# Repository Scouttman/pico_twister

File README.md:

# pico_twister
A simple BLDC motor driver based on the RP2040
Developed using kicad nightly and seem to crash current kicad release(as of 2022)
Currently non functional and just added current sense

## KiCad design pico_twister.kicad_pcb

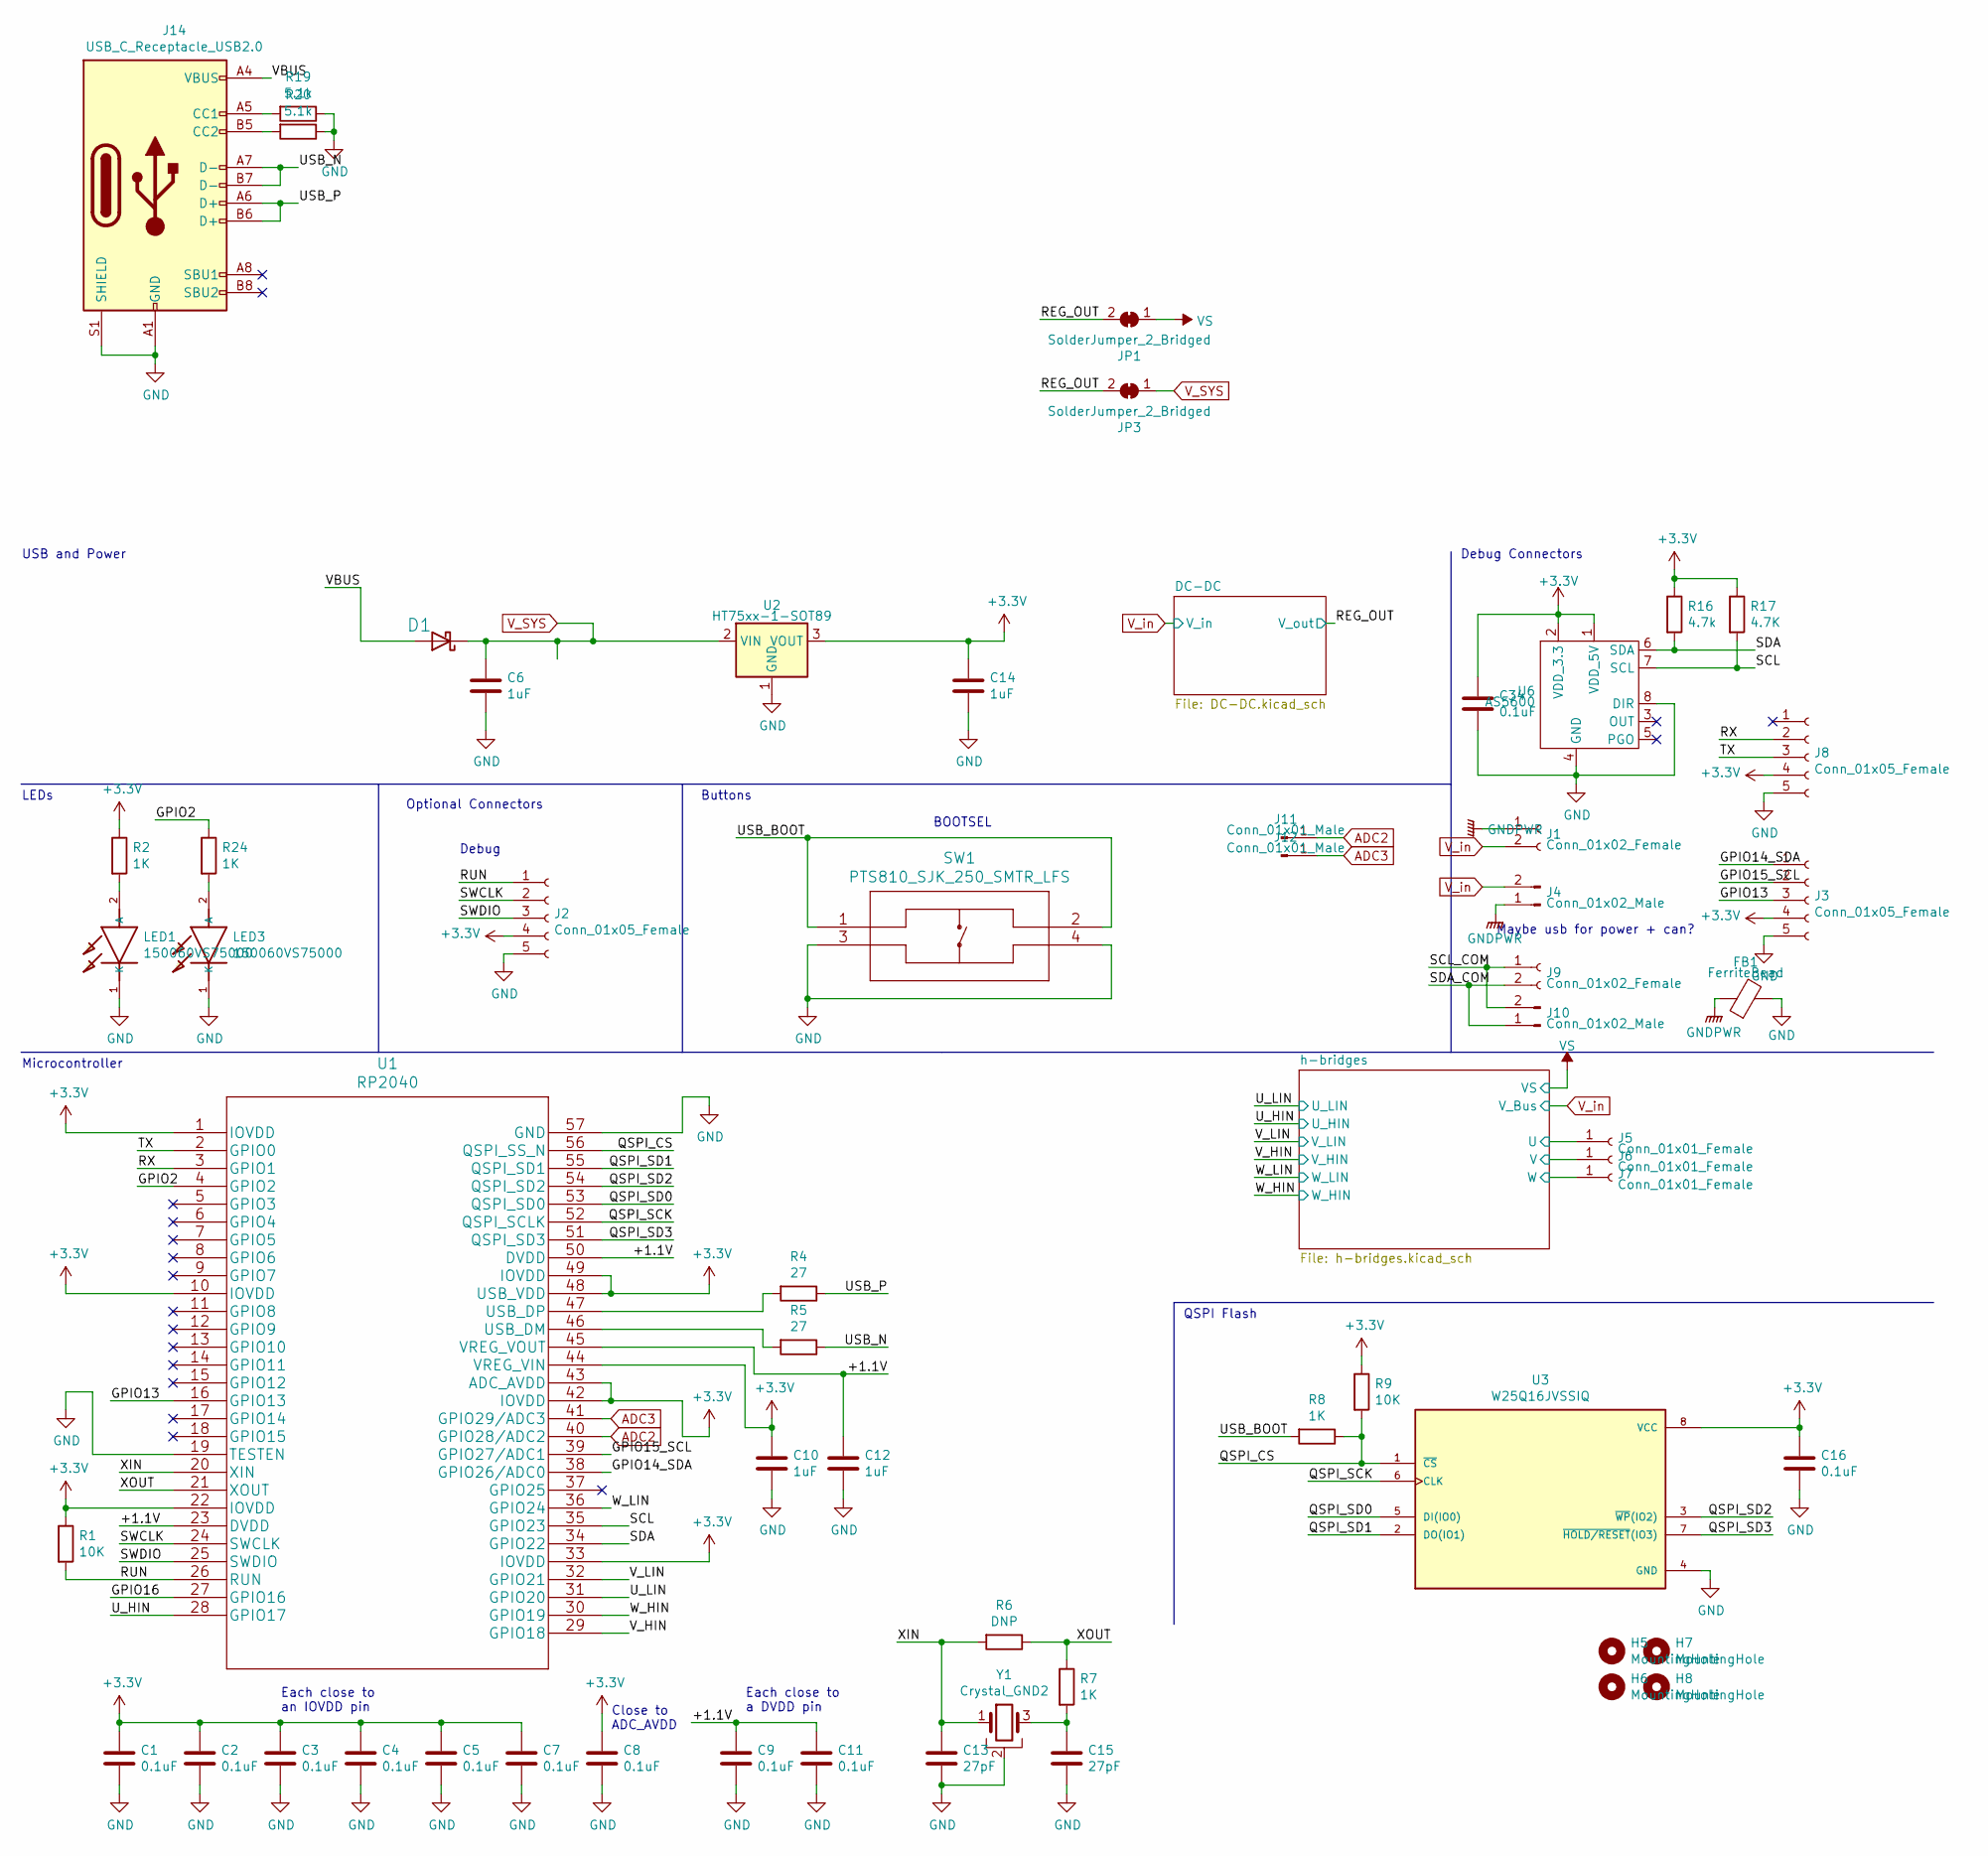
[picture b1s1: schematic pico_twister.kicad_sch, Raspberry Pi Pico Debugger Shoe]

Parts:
C1, C2, C3, C4, C5, C7, C8, C9, C11, C16, C34: 0.1uF; C_0603_1608Metric_Pad1.08x0.95mm_HandSolder; Digi-Key_PN 311-1344-1-ND
C6, C10, C12, C14: 1uF; C_0603_1608Metric_Pad1.08x0.95mm_HandSolder; Digi-Key_PN 1276-6524-1-ND
C13, C15: 27pF; C_0603_1608Metric_Pad1.08x0.95mm_HandSolder; Digi-Key_PN 311-1063-1-ND
D1: B5819W SL; D_SOD-123; LCSC C8598
FB1: FerriteBead; R_0603_1608Metric; LCSC Part C1002
H5, H6, H7, H8: MountingHole; MountingHole_3.2mm_M3
J1: Conn_01x02_Female; AMASS_XT30PW-F_1x02_P2.50mm_Horizontal
J2, J3, J8: Conn_01x05_Female; JST_SH_SM05B-SRSS-TB_1x05-1MP_P1.00mm_Horizontal; LCSC Part C145957
J4: Conn_01x02_Male; AMASS_XT30PW-M_1x02_P2.50mm_Horizontal
J5, J6, J7: Conn_01x01_Female; Pin_D1.4mm_L8.5mm_W2.8mm_FlatFork
J9: Conn_01x02_Female
J10: Conn_01x02_Male
J11, J12: Conn_01x01_Male; TestPoint_Pad_1.0x1.0mm
J14: USB_C_Receptacle_USB2.0; USB_C_Receptacle_XKB_U262-16XN-4BVC11; LCSC Part C167321
JP1, JP3: SolderJumper_2_Bridged; SolderJumper-2_P1.3mm_Bridged_RoundedPad1.0x1.5mm
LED1: 150060VS75000; LED_0805_2012Metric; MOUSER_PART_NUMBER 710-150060VS75000
LED3: 150060VS75000; LED_0805_2012Metric_Castellated; MOUSER_PART_NUMBER 710-150060VS75000
R1, R9: 10K; R_0603_1608Metric_Pad0.98x0.95mm_HandSolder; Digi-Key_PN 311-10KGRCT-ND
R2, R24: 1K; R_0603_1608Metric; Digi-Key_PN 311-1.00KHRCT-ND
R4, R5: 27; R_0603_1608Metric_Pad0.98x0.95mm_HandSolder; Digi-Key_PN 311-27.0HRCT-ND
R6: DNP; R_0603_1608Metric_Pad0.98x0.95mm_HandSolder
R7, R8: 1K; R_0603_1608Metric_Pad0.98x0.95mm_HandSolder; Digi-Key_PN 311-1.00KHRCT-ND
R16: 4.7k; R_0603_1608Metric_Pad0.98x0.95mm_HandSolder; LCSC Part C23162
R17: 4.7K; R_0603_1608Metric_Pad0.98x0.95mm_HandSolder; LCSC Part C23162
R19, R20: 5.1k; R_0603_1608Metric; LCSC Part C23186
SW1: PTS810_SJK_250_SMTR_LFS; SW_SPST_PTS810; Digi-Key_PN CKN10503CT-ND
U1: RP2040; Digi-Key_PN TBD
U2: HT75xx-1-SOT89; SOT-89-3; LCSC Part C14289
U3: W25Q16JVSSIQ; SOIC127P790X216-8N; Digi-Key_PN 256-W25Q16JVSSIM-ND
U6: AS5600; SOIC-8_3.9x4.9mm_P1.27mm
Y1: Crystal_GND2; Crystal_SMD_3225-4Pin_3.2x2.5mm; LCSC Part C9002

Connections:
/+1.1V: C9.1, C11.1, C12.1, U1.23 (DVDD), U1.45 (VREG_VOUT), U1.50 (DVDD)
/GPIO2: R24.1, U1.4 (GPIO2)
/GPIO13: J3.3, U1.16 (GPIO13)
/GPIO14_SDA: J3.1, U1.38 (GPIO26/ADC0)
/GPIO15_SCL: J3.2, U1.39 (GPIO27/ADC1)
/GPIO16: U1.27 (GPIO16)
/QSPI_CS: R8.1, R9.2, U1.56 (QSPI_SS_N), U3.1 (~CS)
/QSPI_SCK: U1.52 (QSPI_SCLK), U3.6 (CLK)
/QSPI_SD0: U1.53 (QSPI_SD0), U3.5 (DI(IO0))
/QSPI_SD1: U1.55 (QSPI_SD1), U3.2 (DO(IO1))
/QSPI_SD2: U1.54 (QSPI_SD2), U3.3 (~WP(IO2))
/QSPI_SD3: U1.51 (QSPI_SD3), U3.7 (~HOLD/RESET(IO3))
/REG_OUT: JP1.2 (B), JP3.2 (B); also elsewhere on the board
/RUN: J2.1, R1.2, U1.26 (RUN)
/RX: J8.2, U1.3 (GPIO1)
/SCL: R17.2, U1.35 (GPIO23), U6.7 (SCL)
/SDA: R16.2, U1.34 (GPIO22), U6.6 (SDA)
/SWCLK: J2.2, U1.24 (SWCLK)
/SWDIO: J2.3, U1.25 (SWDIO)
/TX: J8.3, U1.2 (GPIO0)
/USB_BOOT: R8.2, SW1.1, SW1.2
/USB_N: J14.A7 (D-), J14.B7 (D-), R5.1
/USB_P: J14.A6 (D+), J14.B6 (D+), R4.1
/U_HIN: U1.28 (GPIO17); also elsewhere on the board
/U_LIN: U1.31 (GPIO20); also elsewhere on the board
/VBUS: D1.2 (A), J14.A4 (VBUS), J14.A9 (VBUS), J14.B4 (VBUS), J14.B9 (VBUS)
/V_HIN: U1.29 (GPIO18); also elsewhere on the board
/V_LIN: U1.32 (GPIO21); also elsewhere on the board
/W_HIN: U1.30 (GPIO19); also elsewhere on the board
/W_LIN: U1.36 (GPIO24); also elsewhere on the board
/XIN: C13.1, R6.2, U1.20 (XIN), Y1.1
/XOUT: R6.1, R7.1, U1.21 (XOUT)
/h-bridges/VS_U: J5.1; also elsewhere on the board
/h-bridges/VS_V: J6.1; also elsewhere on the board
/h-bridges/VS_W: J7.1; also elsewhere on the board
ADC2: J11.1, U1.40 (GPIO28/ADC2); also elsewhere on the board
ADC3: J12.1, U1.41 (GPIO29/ADC3)
GND: C1.2, C2.2, C3.2, C4.2, C5.2, C6.2, C7.2, C8.2, C9.2, C10.2, C11.2, C12.2, C13.2, C14.2, C15.2, C16.2, C34.2, FB1.2, J2.5, J3.5, J8.5, J14.A1 (GND), J14.A12 (GND), J14.B1 (GND), J14.B12 (GND), J14.S1 (SHIELD), LED1.1 (K), LED3.1 (K), R19.1, R20.1, SW1.3, SW1.4, U1.19 (TESTEN), U1.57 (GND), U2.1 (GND), U3.4 (GND), U6.4 (GND), U6.8 (DIR), Y1.2; also elsewhere on the board
GNDPWR: FB1.1, J1.1, J4.1; also elsewhere on the board
unnamed: C15.1, R7.2, Y1.3
unnamed: J9.2, J10.1
unnamed: J9.1, J10.2
unnamed: J14.A5 (CC1), R19.2
unnamed: J14.B5 (CC2), R20.2
unnamed: LED1.2 (A), R2.2
unnamed: LED3.2 (A), R24.2
unnamed: R5.2, U1.46 (USB_DM)
unnamed: R4.2, U1.47 (USB_DP)
VS: JP1.1 (A); also elsewhere on the board
V_SYS: C6.1, D1.1 (K), JP3.1 (A), U2.2 (VIN)
V_in: J1.2, J4.2; also elsewhere on the board

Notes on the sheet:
Optional Connectors
USB and Power
Debug Connectors
QSPI Flash
Debug
Each close to a DVDD pin
Buttons
LEDs
Each close to an IOVDD pin
Maybe usb for power + can?
Close to ADC_AVDD
Microcontroller
BOOTSEL

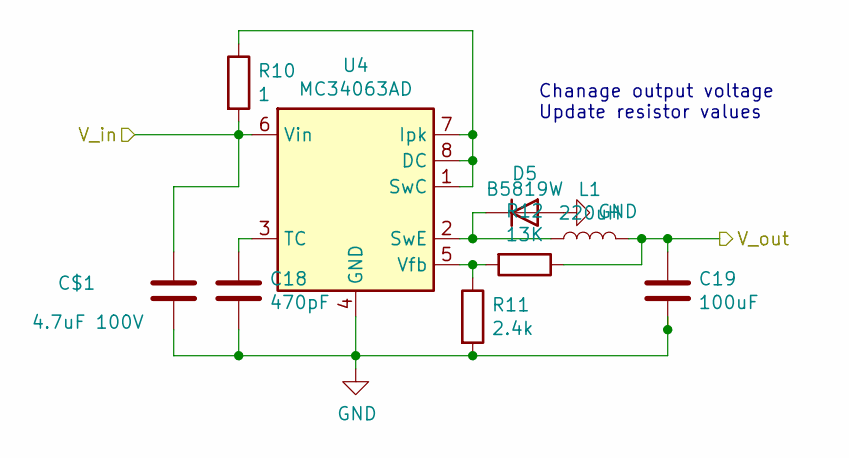
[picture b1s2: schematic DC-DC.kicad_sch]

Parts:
C18: 470pF; C_0603_1608Metric; LCSC Part C1620
C19: 100uF; C_1206_3216Metric; LCSC Part C312983
C$1: 4.7uF 100V; C_1210_3225Metric; LCSC C697607
D5: B5819W; D_SOD-123; LCSC Part C8598
L1: 220uH; SCCD43; LCSC Part C532867
R10: 1; R_0603_1608Metric; LCSC Part C22936
R11: 2.4k; R_0603_1608Metric; LCSC Part C22940
R12: 13K; R_0603_1608Metric; LCSC Part C22797
U4: MC34063AD; SOIC-8_3.9x4.9mm_P1.27mm; LCSC Part C32078

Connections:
/REG_OUT: C19.2, L1.2, R12.1; also elsewhere on the board
GND: C18.2, C19.1, C$1.2, D5.2 (A), R11.2, U4.4 (GND); also elsewhere on the board
unnamed: D5.1 (K), L1.1, U4.2 (SwE)
unnamed: R10.1, U4.1 (SwC), U4.7 (Ipk), U4.8 (DC)
unnamed: C18.1, U4.3 (TC)
unnamed: R11.1, R12.2, U4.5 (Vfb)
V_in: C$1.1, R10.2, U4.6 (Vin); also elsewhere on the board

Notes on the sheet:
Chanage output voltage Update resistor values

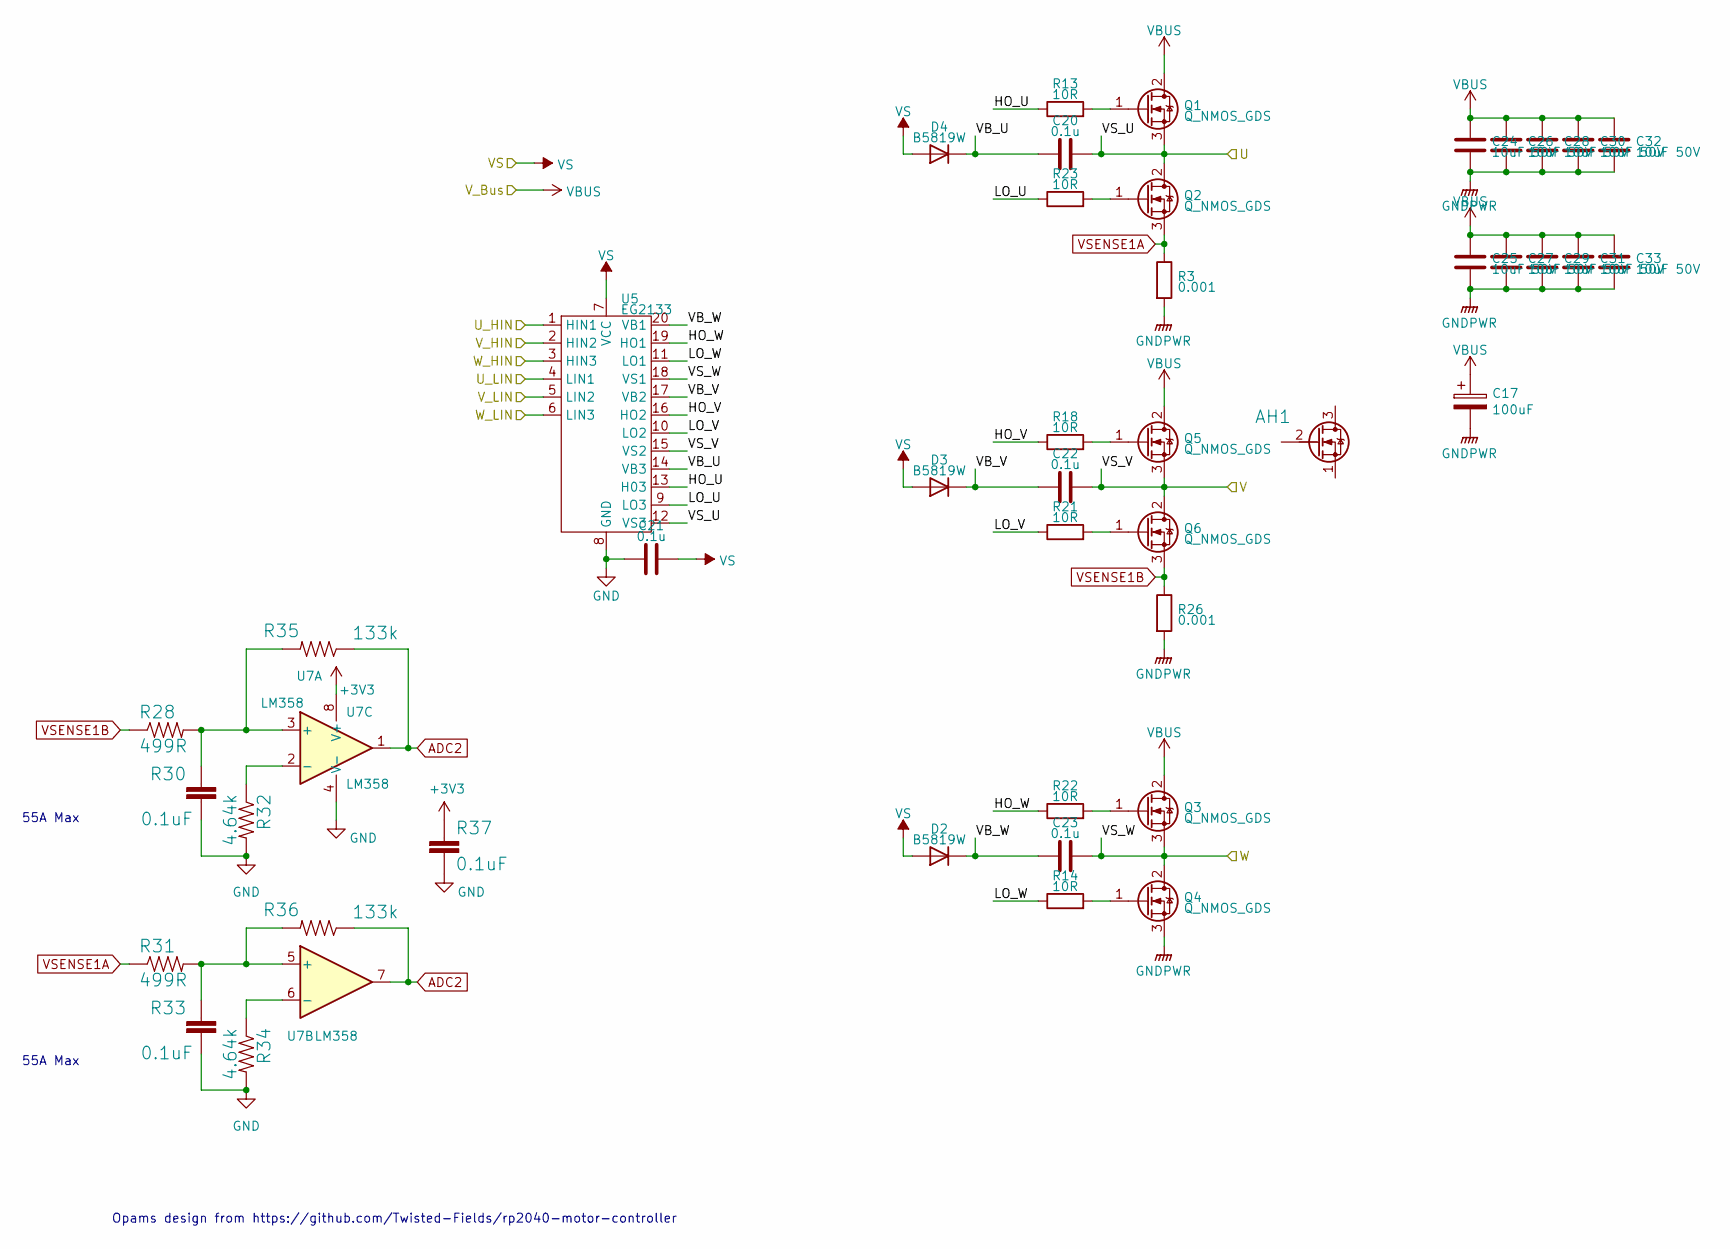
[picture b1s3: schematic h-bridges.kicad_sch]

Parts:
AH1: MOSFETSO-8; PowerPAK_SO-8_123; LCSC C180959
C17: 100uF; CP_Elec_8x10.5; LCSC Part C3352
C20, C21, C22, C23: 0.1u; C_0603_1608Metric; LCSC Part C14858
C24, C25, C26, C27, C28, C29, C30, C31, C32, C33: 10uF 50V; C_1206_3216Metric; LCSC Part C13585
D2, D3, D4: B5819W; D_SOD-123; LCSC Part C8598
Q1, Q2, Q3, Q4, Q5, Q6: Q_NMOS_GDS; DFN-8-1EP_6x5mm_P1.27mm_EP4x4mm; LCSC Part C2758411
R3, R26: 0.001; R_1210_3225Metric; LCSC Part C127695
R13, R14, R18, R21, R22, R23: 10R; R_0603_1608Metric; LCSC Part C22859
R28, R31: 499R; R_0603_1608Metric; LCSC C101076
R30, R37: 0.1uF; C_0603_1608Metric
R32, R34: 4.64k; R_0603_1608Metric; LCSC C144652
R33: 0.1uF; C_0603_1608Metric; LCSC C14663
R35, R36: 133k; R_0603_1608Metric; LCSC C423080
U5: EG2133; TSSOP-20_4.4x6.5mm_P0.65mm; LCSC Part C190343
U7: LM358; MSOP-8_3x3mm_P0.65mm; LCSC C54867

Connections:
/U_HIN: U5.1 (HIN1); also elsewhere on the board
/U_LIN: U5.4 (LIN1); also elsewhere on the board
/V_HIN: U5.2 (HIN2); also elsewhere on the board
/V_LIN: U5.5 (LIN2); also elsewhere on the board
/W_HIN: U5.3 (HIN3); also elsewhere on the board
/W_LIN: U5.6 (LIN3); also elsewhere on the board
/h-bridges/HO_U: R13.1, U5.13 (H03)
/h-bridges/HO_V: R18.1, U5.16 (HO2)
/h-bridges/HO_W: R22.1, U5.19 (HO1)
/h-bridges/LO_U: R23.1, U5.9 (LO3)
/h-bridges/LO_V: R21.1, U5.10 (LO2)
/h-bridges/LO_W: R14.1, U5.11 (LO1)
/h-bridges/VB_U: C20.1, D4.1 (K), U5.14 (VB3)
/h-bridges/VB_V: C22.1, D3.1 (K), U5.17 (VB2)
/h-bridges/VB_W: C23.1, D2.1 (K), U5.20 (VB1)
/h-bridges/VS_U: C20.2, Q1.3 (S), Q2.2 (D), U5.12 (VS3); also elsewhere on the board
/h-bridges/VS_V: C22.2, Q5.3 (S), Q6.2 (D), U5.15 (VS2); also elsewhere on the board
/h-bridges/VS_W: C23.2, Q3.3 (S), Q4.2 (D), U5.18 (VS1); also elsewhere on the board
ADC2: R35.1, R36.1, U7.1, U7.7; also elsewhere on the board
GND: C21.2, R30.2, R32.2, R33.2, R34.2, R37.2, U5.8 (GND), U7.4 (V-); also elsewhere on the board
GNDPWR: C17.2, C24.2, C25.2, C26.2, C27.2, C28.2, C29.2, C30.2, C31.2, C32.2, C33.2, Q4.3 (S), R3.2, R26.2; also elsewhere on the board
unnamed: Q1.1 (G), R13.2
unnamed: Q2.1 (G), R23.2
unnamed: Q3.1 (G), R22.2
unnamed: Q4.1 (G), R14.2
unnamed: Q5.1 (G), R18.2
unnamed: Q6.1 (G), R21.2
unnamed: R28.2, R30.1, R35.2, U7.3 (+)
unnamed: R32.1, U7.2 (-)
unnamed: R31.2, R33.1, R36.2, U7.5 (+)
unnamed: R34.1, U7.6 (-)
VS: C21.1, D2.2 (A), D3.2 (A), D4.2 (A), U5.7 (VCC); also elsewhere on the board
VSENSE1A: Q2.3 (S), R3.1, R31.1
VSENSE1B: Q6.3 (S), R26.1, R28.1
V_in: C17.1, C24.1, C25.1, C26.1, C27.1, C28.1, C29.1, C30.1, C31.1, C32.1, C33.1, Q1.2 (D), Q3.2 (D), Q5.2 (D); also elsewhere on the board

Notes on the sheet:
Opams design from https://github.com/Twisted-Fields/rp2040-motor-controller
55A Max

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
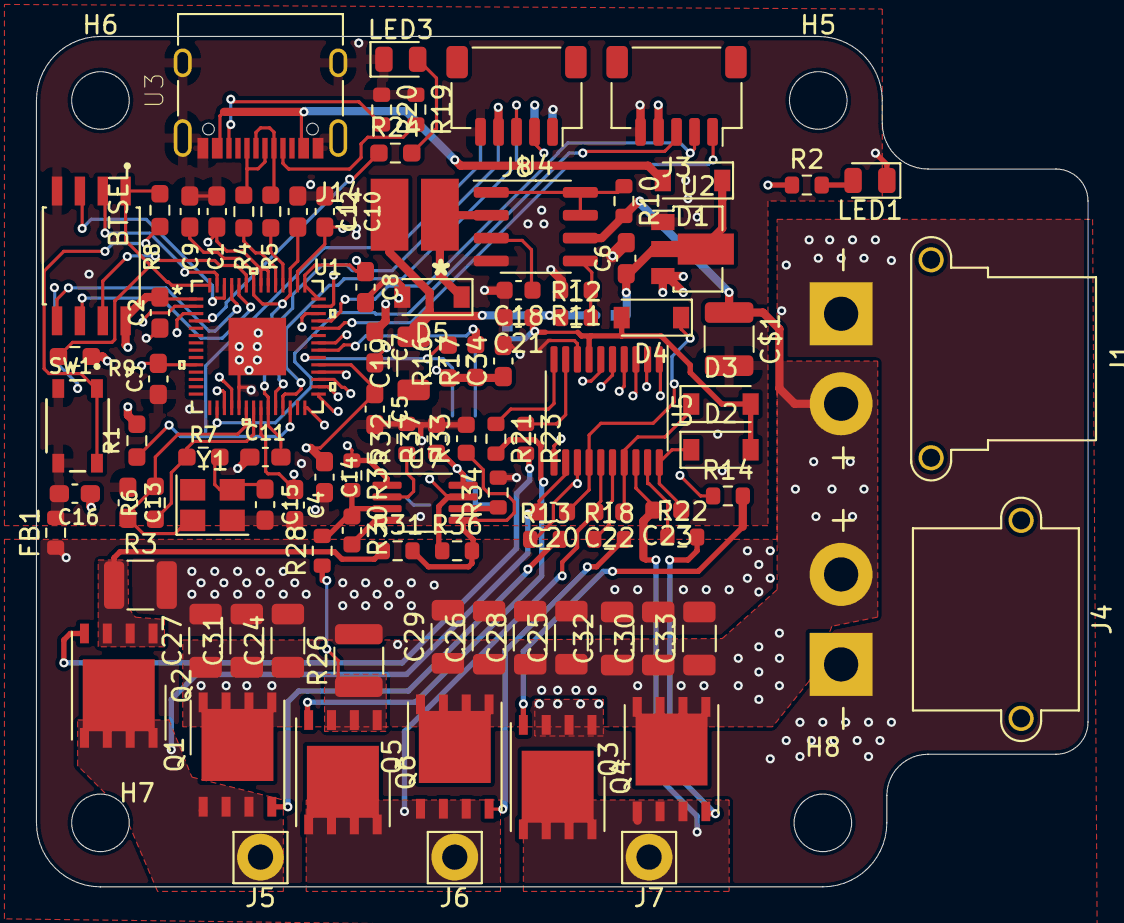
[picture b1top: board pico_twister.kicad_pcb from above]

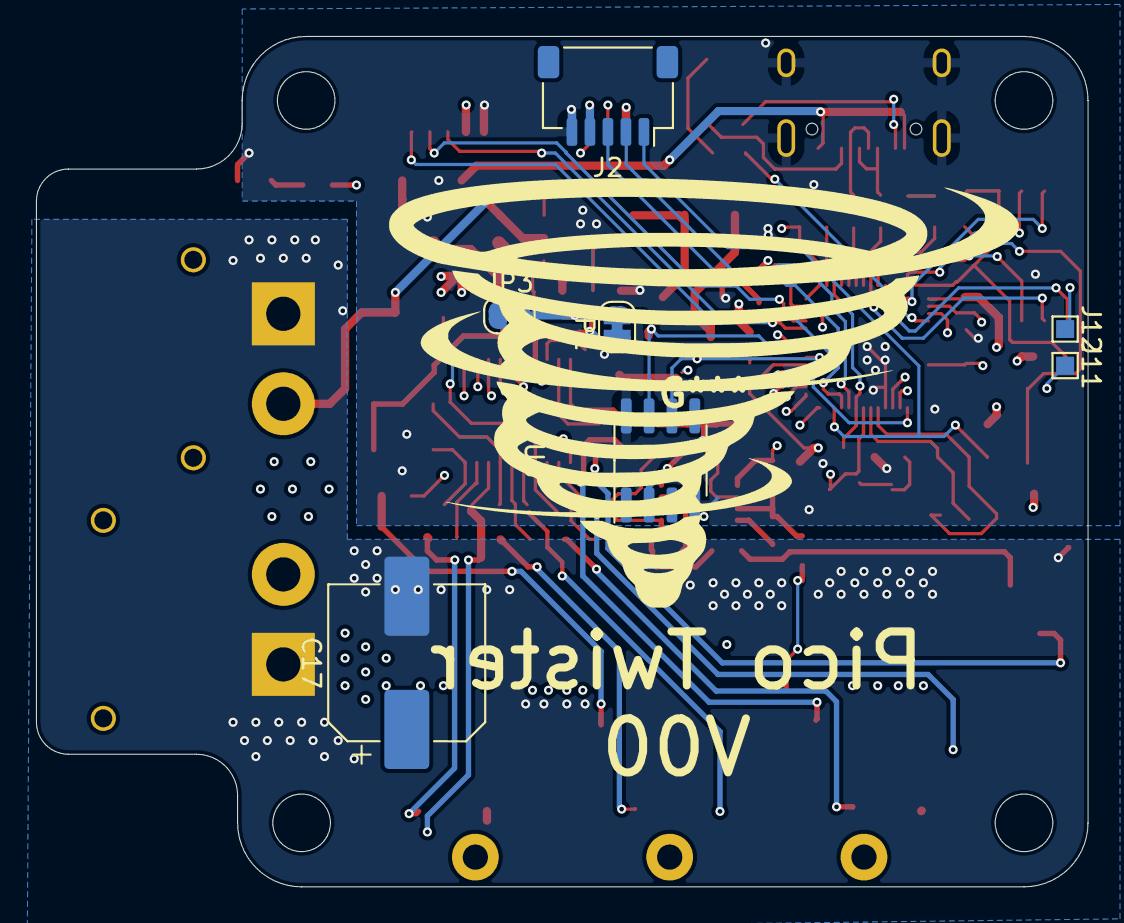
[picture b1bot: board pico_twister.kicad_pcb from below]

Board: 4 copper layers, 58.4 x 47.2 mm, 109 parts (7 on the bottom side), 74 nets.

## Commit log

2022-07-16 inital commit of pcb_files
2022-07-16 added photo

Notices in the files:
pico_twister.kicad_pcb:
https://creativecommons.org/licenses/by/4.0
License: CC BY 4.0
parts and their libraries:
Copyright 2016 Accelerated Designs. All rights reserved.
